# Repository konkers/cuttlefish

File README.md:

# Cuttlefish

An [RP2040](https://www.raspberrypi.com/documentation/microcontrollers/rp2040.html)
based controller for the [LumenPnP Feeder](https://github.com/opulo-inc/feeder).

## Cloning

This repo uses submodule to pull in external dependencies and needs to be recursivly cloned:

```bash
git clone --recurse-submodules https://github.com/konkers/cuttlefish 
```

## PCB

The main pcb is designed in [KiCad](kicad.org).  Becase I use the experimental
HTTP Library support, a nightly version of KiCad is needed.

The [schematic](https://kicanvas.org/?github=https%3A%2F%2Fgithub.com%2Fkonkers%2Fcuttlefish%2Fblob%2Fmain%2Fpcb%2Fmain%2Fcuttlefish-main.kicad_sch) and
[layout](https://kicanvas.org/?github=https%3A%2F%2Fgithub.com%2Fkonkers%2Fcuttlefish%2Fblob%2Fmain%2Fpcb%2Fmain%2Fcuttlefish-main.kicad_pcb)
can be viewed through KiCanvas.

### Front

### Back

## Firmware

Firmware has not been written yet.  Check back for updates.

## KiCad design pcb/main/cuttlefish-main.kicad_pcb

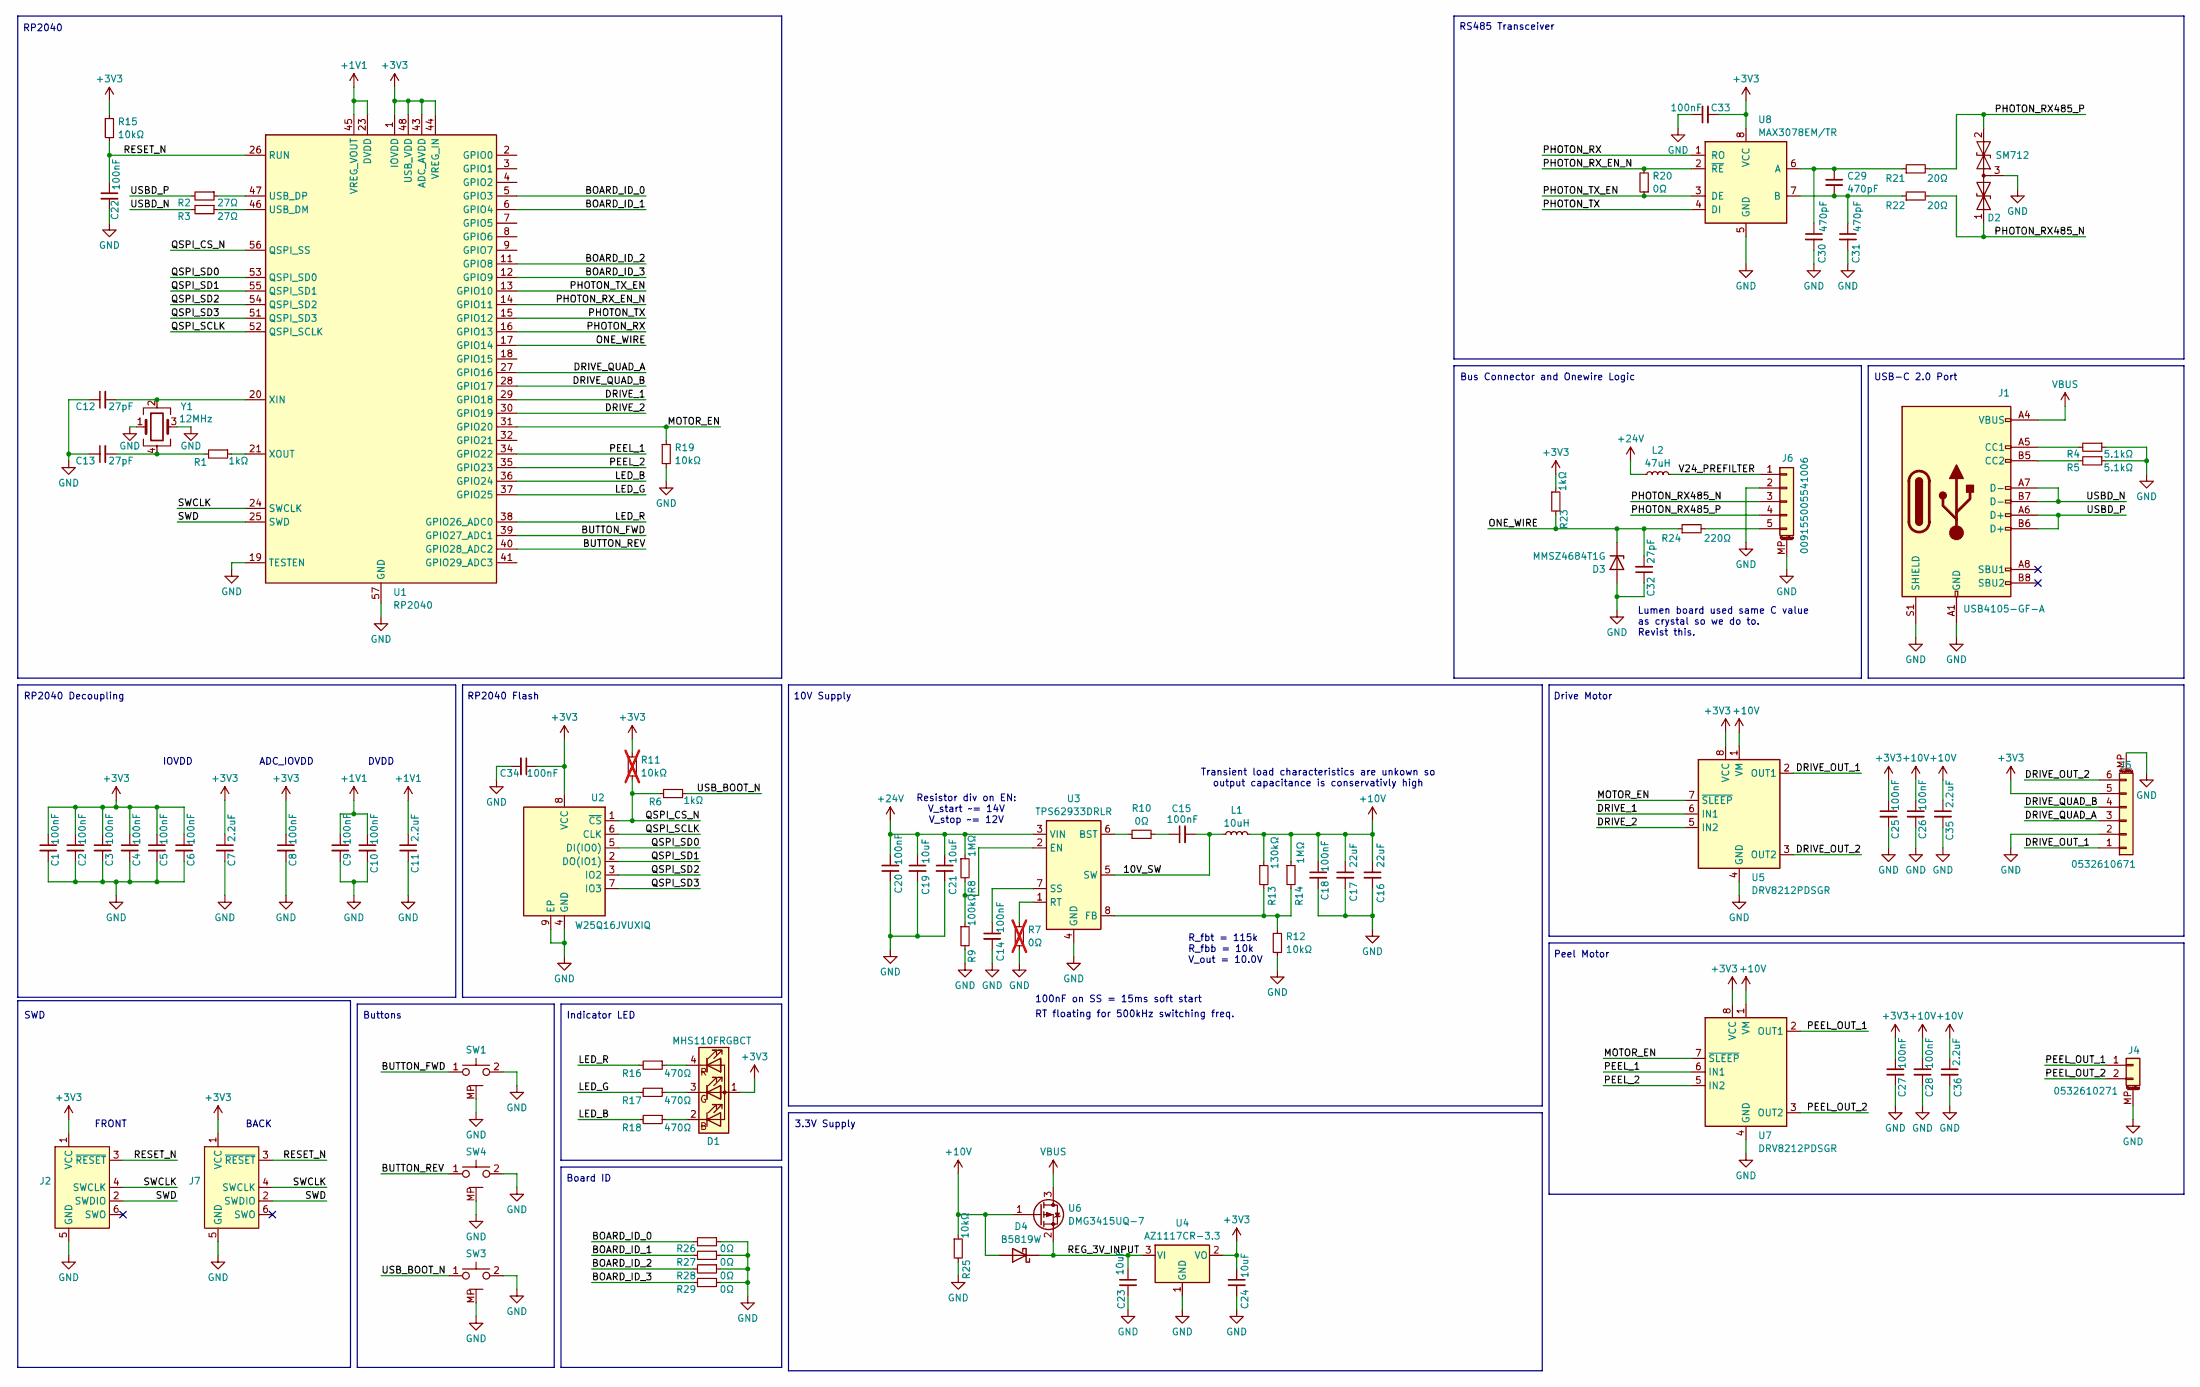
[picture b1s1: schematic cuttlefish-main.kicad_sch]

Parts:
C1, C2, C3, C4, C5, C6, C8, C9, C10, C14, C15, C18, C20, C22, C25, C26, C27, C28, C33, C34: 100nF; C_0402_1005Metric; Rated Voltage 50V; Tolerance ±10%; Part URL /part/12/
C7, C11, C35, C36: 2.2uF; C_0603_1608Metric; Rated Voltage 50V; Tolerance ±10%; Part URL /part/17/
C12, C13, C32: 27pF; C_0402_1005Metric; Tolerance ±5%; Part URL /part/6/
C16, C17: 22uF; C_0805_2012Metric; Rated Voltage 25V; Tolerance ±20%; Part URL /part/28/
C19, C21, C23, C24: 10uF; C_0603_1608Metric; Rated Voltage 35V; Tolerance ±20%; Part URL /part/29/
C29, C30, C31: 470pF; C_0402_1005Metric; Rated Voltage 50V; Tolerance ±10%; Part URL /part/39/
D1: MHS110FRGBCT; MEIHUA_MHS110FRGBCT; Part URL /part/33/
D2: SM712; SOT-23; Breakdown Voltage 13.3V; Clamping Voltage 21V; Part URL /part/41/
D3: MMSZ4684T1G; D_SOD-123; Forward Voltage 900mV@10mA; Rated Voltage 3.3 V; Part URL /part/45/
D4: B5819W; D_SOD-123; Forward Voltage 690mV@1A; Rated Voltage 40 V; Part URL /part/49/
J1: USB4105-GF-A; USB_C_Receptacle_GCT_USB4105-xx-A_16P_TopMnt_Horizontal; Part URL /part/15/
J2: Tag-Connect_TC2030-IDC-NL_2x03_P1.27mm_Vertical
J4: 0532610271; Molex_PicoBlade_53261-0271_1x02-1MP_P1.25mm_Horizontal; Part URL /part/37/
J5: 0532610671; Molex_PicoBlade_53261-0671_1x06-1MP_P1.25mm_Horizontal; Part URL /part/36/
J6: 009155005541006; AVX_009155005541006; Part URL /part/43/
J7: Conn_ARM_SWD_TagConnect_TC2030-NL; Tag-Connect_TC2030-IDC-NL_2x03_P1.27mm_Vertical
L1: 10uH; Inductor_SMD_7.0mm_6.7mm_2.8mm; Tolerance ±20%; Part URL /part/46/
L2: 47uH; L_Sunlord_SWPA5020S; Tolerance ±20%; Part URL /part/42/
R1, R6, R23: 1kΩ; R_0402_1005Metric; Tolerance ±1%; Part URL /part/7/
R2, R3: 27Ω; R_0402_1005Metric; Tolerance ±1%; Part URL /part/8/
R4, R5: 5.1kΩ; R_0402_1005Metric; Tolerance ±1%; Part URL /part/9/
R7: 0Ω; R_0402_1005Metric; Tolerance Jumper; Part URL /part/21/; not fitted
R8, R14: 1MΩ; R_0402_1005Metric; Tolerance ±1%; Part URL /part/24/
R9: 100kΩ; R_0402_1005Metric; Tolerance ±1%; Part URL /part/11/
R10, R20, R26, R27, R28, R29: 0Ω; R_0402_1005Metric; Tolerance Jumper; Part URL /part/21/
R11: 10kΩ; R_0402_1005Metric; Tolerance ±1%; Part URL /part/25/; not fitted
R12, R15, R19, R25: 10kΩ; R_0402_1005Metric; Tolerance ±1%; Part URL /part/25/
R13: 130kΩ; R_0402_1005Metric; Tolerance ±1%; Part URL /part/26/
R16, R17, R18: 470Ω; R_0402_1005Metric; Tolerance ±1%; Part URL /part/34/
R21, R22: 20Ω; R_0402_1005Metric; Tolerance ±1%; Part URL /part/40/
R24: 220Ω; R_0402_1005Metric; Tolerance ±1%; Part URL /part/44/
SW1, SW3, SW4: 1TS003B-2600-3500A-CT; HYP_1TS003B_2600_3500A_CT; Part URL /part/32/
U1: RP2040; QFN-56-1EP_7x7mm_P0.4mm_EP3.2x3.2mm; Rated Voltage 1.8~3.3V; Part URL /part/4/
U2: W25Q16JVUXIQ; USON-8-1EP_3x2mm_P0.5mm_EP0.3x1.7mm; Rated Voltage 2.7~3.6V; Part URL /part/18/
U3: TPS62933DRLR; SOT-583-8; Part URL /part/20/
U4: AZ1117CR-3.3; SOT-89-3; Part URL /part/47/
U5, U7: DRV8212PDSGR; WSON-8-1EP_2x2mm_P0.5mm_EP0.9x1.6mm; Rated Voltage 1.65~5.5V; Part URL /part/35/
U6: DMG3415UQ-7; SOT-23-3; Rated Voltage 20 V; Part URL /part/48/
U8: MAX3078EM/TR; SOIC-8_3.9x4.9mm_P1.27mm; Rated Voltage 3~3.6V; Part URL /part/38/
Y1: 12MHz; Crystal_SMD_3225-4Pin_3.2x2.5mm; Frequency Tolerance ±10ppm; Part URL /part/5/

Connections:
+1V1: C9.1, C10.1, C11.1, U1.23 (DVDD), U1.45 (VREG_VOUT), U1.50 (DVDD)
+3V3: C1.1, C2.1, C3.1, C4.1, C5.1, C6.1, C7.1, C8.1, C24.1, C25.1, C27.1, C33.2, C34.1, D1.1 (A), J2.1 (VCC), J5.5, J7.1 (VCC), R11.1, R15.1, R23.1, U1.1 (IOVDD), U1.10 (IOVDD), U1.22 (IOVDD), U1.33 (IOVDD), U1.42 (IOVDD), U1.43 (ADC_AVDD), U1.44 (VREG_IN), U1.48 (USB_VDD), U1.49 (IOVDD), U2.8 (VCC), U4.2 (VO), U5.8 (VCC), U7.8 (VCC), U8.8 (VCC)
+10V: C16.1, C17.1, C18.1, C26.1, C28.1, C35.1, C36.1, D4.2 (A), L1.2, R13.1, R14.1, R25.1, U5.1 (VM), U6.1 (G), U7.1 (VM)
+24V: C19.1, C20.1, C21.1, L2.1, R8.1, U3.3 (VIN)
/10V_SW: C15.2, L1.1, U3.5 (SW)
/BOARD_ID_0: R26.2, U1.5 (GPIO3)
/BOARD_ID_1: R27.2, U1.6 (GPIO4)
/BOARD_ID_3: R29.2, U1.12 (GPIO9)
/BUTTON_FWD: SW1.1, U1.39 (GPIO27_ADC1)
/BUTTON_REV: SW4.1, U1.40 (GPIO28_ADC2)
/DRIVE_1: U1.29 (GPIO18), U5.6 (IN1)
/DRIVE_2: U1.30 (GPIO19), U5.5 (IN2)
/DRIVE_OUT_1: J5.1, U5.2 (OUT1)
/DRIVE_OUT_2: J5.6, U5.3 (OUT2)
/DRIVE_QUAD_A: J5.3, U1.27 (GPIO16)
/DRIVE_QUAD_B: J5.4, U1.28 (GPIO17)
/LED_B: R18.2, U1.36 (GPIO24)
/LED_G: R17.2, U1.37 (GPIO25)
/LED_R: R16.2, U1.38 (GPIO26_ADC0)
/MOTOR_EN: R19.1, U1.31 (GPIO20), U5.7 (~SLEEP), U7.7 (~SLEEP)
/ONE_WIRE: C32.2, D3.1 (K), R23.2, R24.1, U1.17 (GPIO14)
/PEEL_1: U1.34 (GPIO22), U7.6 (IN1)
/PEEL_2: U1.35 (GPIO23), U7.5 (IN2)
/PEEL_OUT_1: J4.1, U7.2 (OUT1)
/PEEL_OUT_2: J4.2, U7.3 (OUT2)
/PHOTON_RX: U1.16 (GPIO13), U8.1 (RO)
/PHOTON_RX485_N: D2.1 (A1), J6.3, R22.2
/PHOTON_RX485_P: D2.2 (A2), J6.4, R21.2
/PHOTON_RX_EN_N: R20.2, U1.14 (GPIO11), U8.2 (~RE)
/PHOTON_TX: U1.15 (GPIO12), U8.4 (DI)
/PHOTON_TX_EN: R20.1, U1.13 (GPIO10), U8.3 (DE)
/QSPI_CS_N: R6.2, R11.2, U1.56 (QSPI_SS), U2.1 (~CS)
/QSPI_SCLK: U1.52 (QSPI_SCLK), U2.6 (CLK)
/QSPI_SD0: U1.53 (QSPI_SD0), U2.5 (DI(IO0))
/QSPI_SD1: U1.55 (QSPI_SD1), U2.2 (DO(IO1))
/QSPI_SD2: U1.54 (QSPI_SD2), U2.3 (IO2)
/QSPI_SD3: U1.51 (QSPI_SD3), U2.7 (IO3)
/REG_3V_INPUT: C23.1, D4.1 (K), U4.3 (VI), U6.2 (S)
/RESET_N: C22.1, J2.3 (~RESET), J7.3 (~RESET), R15.2, U1.26 (RUN)
/SWCLK: J2.4 (SWCLK), J7.4 (SWCLK), U1.24 (SWCLK)
/SWD: J2.2 (SWDIO), J7.2 (SWDIO), U1.25 (SWD)
/USBD_N: J1.A7 (D-), J1.B7 (D-), R3.2
/USBD_P: J1.A6 (D+), J1.B6 (D+), R2.2
/USB_BOOT_N: R6.1, SW3.1
/V24_PREFILTER: J6.1, L2.2
unnamed: C13.2, R1.2, Y1.4
unnamed: C15.1, R10.2
unnamed: D1.2 (BK), R18.1
unnamed: D1.3 (GK), R17.1
unnamed: D1.4 (RK), R16.1
unnamed: J1.A5 (CC1), R4.2
unnamed: J1.B5 (CC2), R5.2
unnamed: J6.5, R24.2
unnamed: R3.1, U1.46 (USB_DM)
unnamed: R2.1, U1.47 (USB_DP)
unnamed: C12.2, U1.20 (XIN), Y1.2
unnamed: R1.1, U1.21 (XOUT)
unnamed: R10.1, U3.6 (BST)
unnamed: R8.2, R9.1, U3.2 (EN)
unnamed: R12.1, R13.2, R14.2, U3.8 (FB)
unnamed: R7.1, U3.1 (RT)
unnamed: C14.1, U3.7 (SS)
unnamed: C29.1, C30.1, R21.1, U8.6 (A)
unnamed: C29.2, C31.1, R22.1, U8.7 (B)
VBUS: J1.A4 (VBUS), J1.A9 (VBUS), J1.B4 (VBUS), J1.B9 (VBUS), U6.3 (D)

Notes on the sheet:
RP2040
ADC_IOVDD
Board ID
3.3V Supply
R_fbt = 115k R_fbb = 10k V_out = 10.0V
IOVDD
SWD
RP2040 Flash
Drive Motor
Lumen board used same C value as crystal so we do to. Revist this.
RT floating for 500kHz switching freq.
100nF on SS = 15ms soft start
RP2040 Decoupling
Bus Connector and Onewire Logic
DVDD
Resistor div on EN: V_start ~= 14V V_stop ~= 12V
Transient load characteristics are unkown so output capacitance is conservativly high
USB-C 2.0 Port
Buttons
10V Supply
RS485 Transceiver
Indicator LED
Peel Motor
FRONT
BACK

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
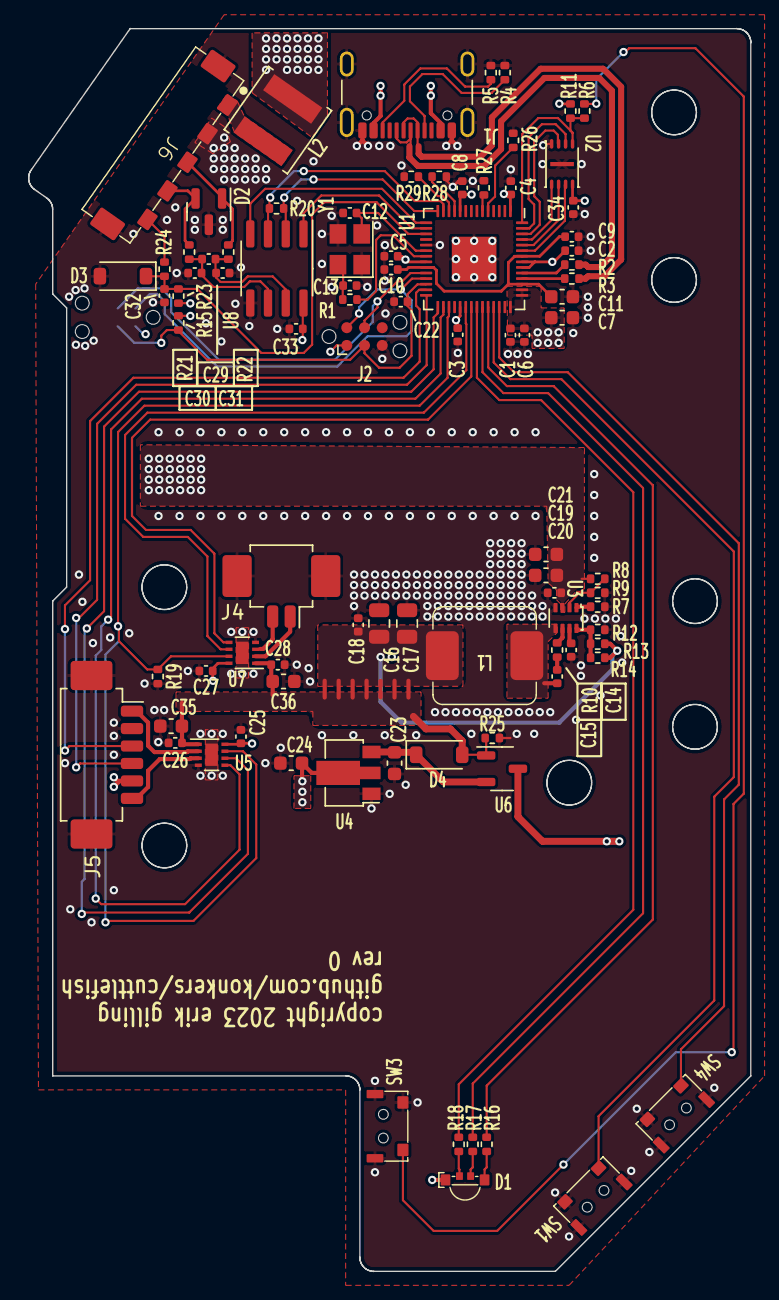
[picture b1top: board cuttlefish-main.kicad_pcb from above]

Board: 4 copper layers, 51.7 x 89.0 mm, 89 parts (1 on the bottom side), 67 nets.

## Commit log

2023-10-30 pcb/main initial schematic capture
2023-11-03 First pass at routing complete
2023-11-08 Almost ready for rev0 fab
2023-11-08 Add content to README.md
2023-11-08 Update third_party/konkers_kicad_lib
2023-11-11 firmware: Add skeleton firmware
2023-11-11 firmware: Add usb serial port.
2023-11-13 firmware: Add picotool reboot to BOOTSEL support.
2023-11-13 firmware: Add USB serial number

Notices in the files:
pcb/main/cuttlefish-main.kicad_pcb:
copyright 2023 erik gilling
